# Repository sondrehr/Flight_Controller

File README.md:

# Flight_Controller
The code used on my STM32 diy drone flight controller

## Installation and running
Download and add the repository https://github.com/rogerclarkmelbourne/Arduino_STM32 to devices folder within the Arduino IDE folder to access the boards hardware settings.
With this done one can use the Arduino IDE to upload the code directly to the board. 

## Drone design
### Drone design v1.0

### Drone design v2.0

Redesigned most parts and added lidar and another GPS.

## Circuit board 
### Circuit board v1.0(left) vs v2.0(right)

#### Backside
Focused on more solid soldering. In addition to cleaning up in v2.0

#### Frontside
Added more light to display different states in v2.0

### Circuit board v3.0

This is going to be a PCB instead a diy soldered board

#### Schematic made in KiCad

#### PCB model made in KiCad

Made on a 4 layer PCB where layer 2 and 3(not included in the img) are VCC and GND. The traces are roughly split into a vertical layer(1) and horizontal layer(4) to make tracing easier.

#### 3D model from KiCad

#### Picture of PCB v3.0 with soldered components

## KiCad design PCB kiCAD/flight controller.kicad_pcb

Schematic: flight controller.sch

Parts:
D1, D2, D3, D4: LED; LED_D4.0mm
J1: ESC3; PinHeader_1x03_P2.54mm_Horizontal
J2: ESC4; PinHeader_1x03_P2.54mm_Horizontal
J3: LED4; PinHeader_1x02_P2.54mm_Horizontal
J4: LED3; PinHeader_1x02_P2.54mm_Horizontal
J5: LED1; PinHeader_1x02_P2.54mm_Horizontal
J6: ESC1; PinHeader_1x03_P2.54mm_Horizontal
J7: LED2; PinHeader_1x02_P2.54mm_Horizontal
J8: ESC2; PinHeader_1x03_P2.54mm_Horizontal
J9: Lidar; PinHeader_1x04_P2.54mm_Horizontal
J10: RX; PinHeader_1x03_P2.54mm_Horizontal
J11: V_BATT; PinHeader_1x01_P2.54mm_Horizontal
R1, R2, R3, R4: 100; R_Axial_DIN0411_L9.9mm_D3.6mm_P12.70mm_Horizontal
R5: 1k; R_Axial_DIN0411_L9.9mm_D3.6mm_P12.70mm_Horizontal
R6: 10k; R_Axial_DIN0411_L9.9mm_D3.6mm_P12.70mm_Horizontal
U1: YAAJ_BluePill_Part_Like; YAAJ_BluePill_1
U2, U7: mpu6050pcb; IMU
U3: FTDI; Socket_Strip_Angled_1x06_Pitch2.54mm
U4, U5: gps; GPS
U6: Barometer

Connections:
/3V3: U1.20 (3V3), U6.2 (3V3), U7.7
/5V: J5.2, J6.2, J9.2, J10.2, U1.18 (5V), U2.1, U3.3 (VCC), U4.1 (VCC), U5.1 (VCC), U7.1
/BLUE_LED: R4.1, U1.11 (PB3)
/ESC1: J6.3, U1.14 (PB6)
/ESC2: J8.3, U1.15 (PB7)
/ESC3: J1.3, U1.16 (PB8)
/ESC4: J2.3, U1.17 (PB9)
/GREEN_LED: R2.1, U1.8 (PA11)
/PPM: J10.3, U1.25 (PA0)
/RED_LED: R1.1, U1.9 (PA12)
/RX: U1.6 (PA9), U3.5 (RX), U5.2 (RX)
/RX2: U1.27 (PA2), U4.2 (RX)
/SCL: J9.3, U1.35 (PB10), U2.3, U4.5 (SCL), U6.4 (SCL), U7.3
/SDA: J9.4, U1.36 (PB11), U2.4, U4.6 (SDA), U6.3 (SDA), U7.4
/TX: U1.7 (PA10), U3.4 (TX), U5.3 (TX)
/TX2: U1.28 (PA3), U4.3 (TX)
/VOLTAGE: R5.1, R6.1, U1.29 (PA4)
/YELLOW_LED: R3.1, U1.10 (PA15)
Earth: D1.1 (K), D2.1 (K), D3.1 (K), D4.1 (K), J1.1, J2.1, J3.1, J4.1, J5.1, J6.1, J7.1, J8.1, J9.1, J10.1, R5.2, U1.19 (GND), U1.39 (GND), U1.40 (GND), U2.2, U3.1 (GND), U4.4 (GND), U5.4 (GND), U6.1 (GND), U7.2
unnamed: D1.2 (A), R1.2
unnamed: D2.2 (A), R2.2
unnamed: D3.2 (A), R3.2
unnamed: D4.2 (A), R4.2
unnamed: J1.2, J4.2
unnamed: J2.2, J3.2
unnamed: J7.2, J8.2
unnamed: J11.1, R6.2

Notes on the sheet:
Lights
Voltage measurement
To control the drone
To upload code to stm32
FTDI
Lidar
Barometer
GPS
IMUs
DIV
Blue Pill
Connections
Sensors

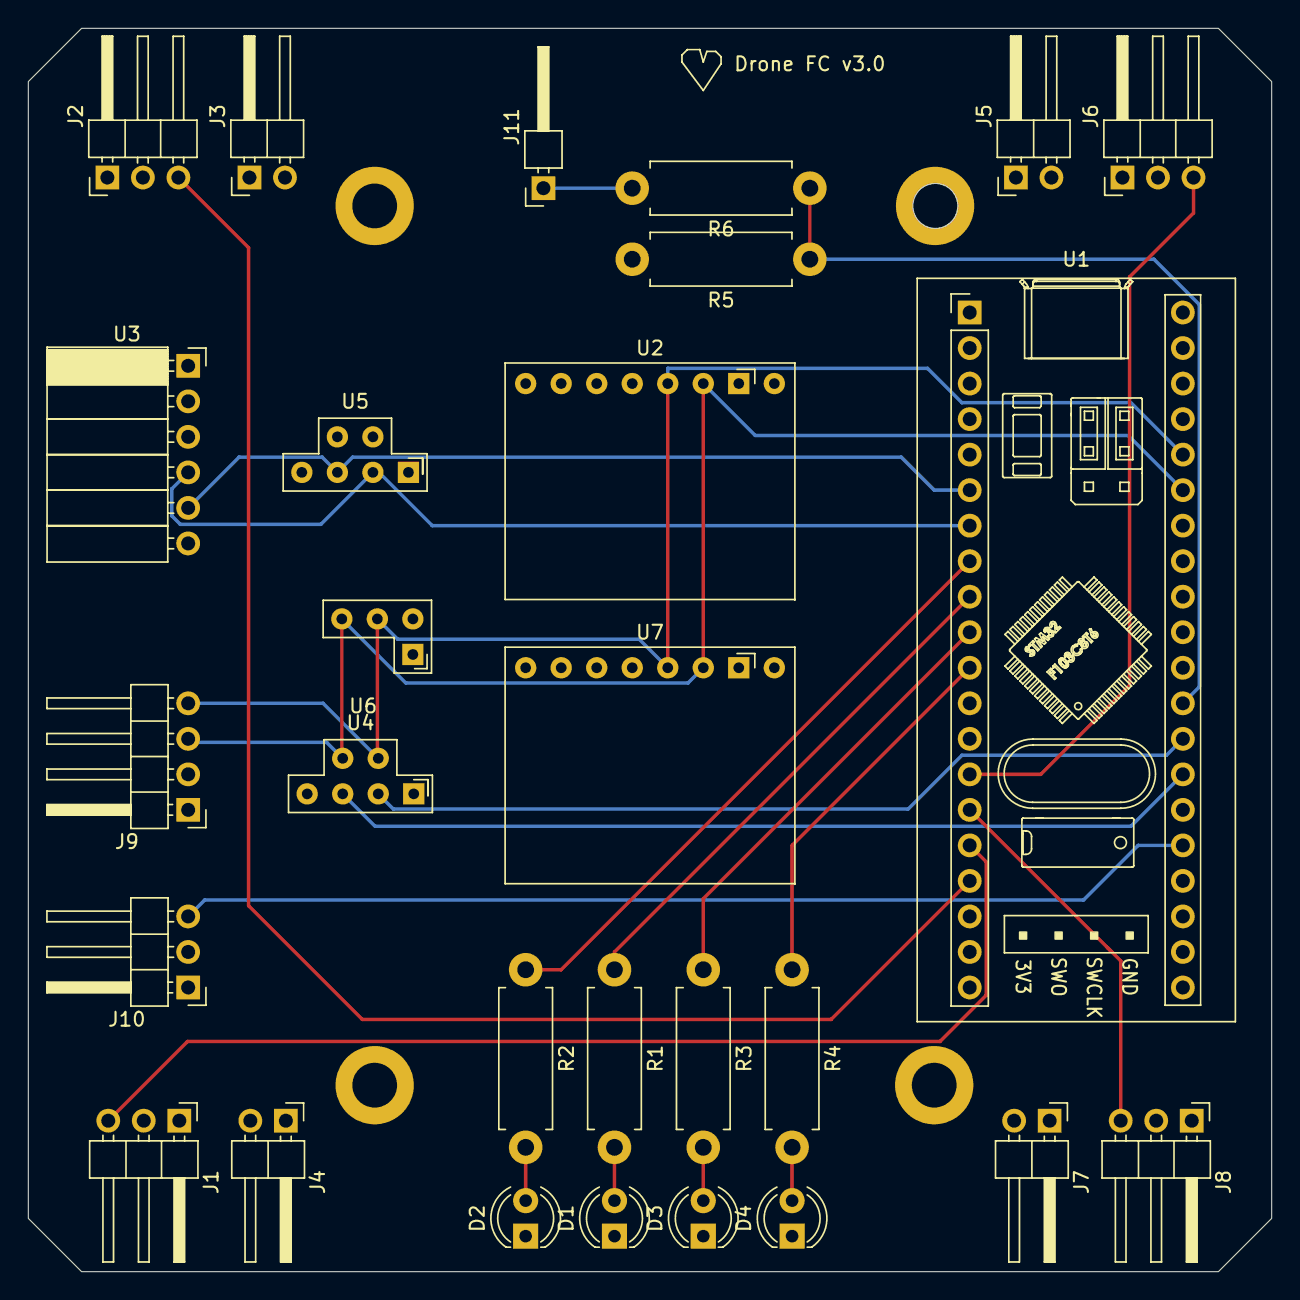
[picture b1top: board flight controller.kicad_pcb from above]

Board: 4 copper layers, 88.9 x 88.9 mm, 28 parts (0 on the bottom side), 27 nets.

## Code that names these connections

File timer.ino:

//Modifiserer timer_setup() filene
///////////////////////////////////////////////////////////////////////////////////////////

void timer_setup() {
  Timer2.attachCompare1Interrupt(handler_channel_1);                          //utfører handler_channel_1 når det blir interrupted
  TIMER2_BASE->CR1 = TIMER_CR1_CEN;                                           
  TIMER2_BASE->CR2 = 0;
  TIMER2_BASE->SMCR = 0;
  TIMER2_BASE->DIER = TIMER_DIER_CC1IE;                                       //Gjør det mulig å attache en interrupt (capture compare 1 interrupt enable)     
  TIMER2_BASE->EGR = 0;
  TIMER2_BASE->CCMR1 = TIMER_CCMR1_CC1S_INPUT_TI1;                            //Koble reciever input til timeren som brukes for å finne en rising edge
  TIMER2_BASE->CCMR2 = 0;
  TIMER2_BASE->CCER = TIMER_CCER_CC1E;

  TIMER2_BASE->CCER &= ~TIMER_CCER_CC1P;                                      //Brukes for detektere enn stigende edge
  TIMER2_BASE->PSC = 71;                                                      //Prescaler som skalerer hastigheten på timeren ned til 1 MHz
  TIMER2_BASE->ARR = 0xFFFF;                                                  //auto reload: Hvor lang tid timeren bruker på en runde
  TIMER2_BASE->DCR = 0;



//Output til ESC
/////////////////////////////////////////////////////////////////////////////////////////////

  TIMER4_BASE->CR1 = TIMER_CR1_CEN | TIMER_CR1_ARPE;
  TIMER4_BASE->CR2 = 0;
  TIMER4_BASE->SMCR = 0;
  TIMER4_BASE->DIER = 0;
  TIMER4_BASE->EGR = 0;
  TIMER4_BASE->CCMR1 = (0b110 << 4) | TIMER_CCMR1_OC1PE | (0b110 << 12) | TIMER_CCMR1_OC2PE;
  TIMER4_BASE->CCMR2 = (0b110 << 4) | TIMER_CCMR2_OC3PE | (0b110 << 12) | TIMER_CCMR2_OC4PE;
  TIMER4_BASE->CCER = TIMER_CCER_CC1E | TIMER_CCER_CC2E | TIMER_CCER_CC3E | TIMER_CCER_CC4E;
  
  TIMER4_BASE->PSC = 71;
  TIMER4_BASE->ARR = 5000;                                              //Hvor mange mikrosekunder den skal gå (auto reload value)
  TIMER4_BASE->DCR = 0;                                            

  TIMER4_BASE->CCR1 = 1000;                                             //Output er høy til timeren kommer til <- antall mikrosekunder
  TIMER4_BASE->CCR2 = 1000;                                             //4 ulike timere som blir reset av programmet og ikke ARR
  TIMER4_BASE->CCR3 = 1000;
  TIMER4_BASE->CCR4 = 1000;
  pinMode(PB6, PWM);                                                    //PB6 er standard output for timer 4 channel 1
  pinMode(PB7, PWM);
  pinMode(PB8, PWM);
  pinMode(PB9, PWM);
}

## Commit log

2020-01-18 første commit
2020-01-18 rettelse
2020-01-18 fjernet //
2020-01-18 La til //
2020-01-18 La til bilder
2020-01-18 Fjernet bilder
2020-01-21 Diverse småfeil og la til kommentarer
2020-01-21 La til bilder og film
2020-01-22 Fikset litt diverse småfeil
2021-11-14 Endringer gjort i Sommer
2021-11-14 ReadMe
2021-11-14 picture
2021-11-14 pictures
2021-11-14 readme2
2021-11-14 cropped pictures
2021-11-14 resize
2021-11-14 resize2
2021-11-14 resize3
2021-11-14 cleanup
2021-11-16 pcb schematic
2021-11-16 pcb cleanup
2021-11-16 space
2021-11-16 header
2021-11-21 pcb and 3d modell
2021-11-21 fix schematic png
2021-11-21 fix readme
2021-11-21 text readme
2021-11-21 text
2021-11-21 revise pcb
2022-01-11 ny pcb
2022-01-11 fikse bilder
2022-01-11 pcv v3
2022-01-11 pcb v3
2022-01-11 bold
2022-01-11 fikse fokus
2024-04-07 added step files
